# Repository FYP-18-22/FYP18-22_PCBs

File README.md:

This repository holds all our electrical and electronics designs.

Contains files for a main PCB and an actuation PCB.

The main PCB uses an STM32F103CC controller and provides for interfacing with various sensors. It also interacts with our actuation PCB by accepting the zero-crossing detection signal from the actuation PCB and sends back actuation commands to it.

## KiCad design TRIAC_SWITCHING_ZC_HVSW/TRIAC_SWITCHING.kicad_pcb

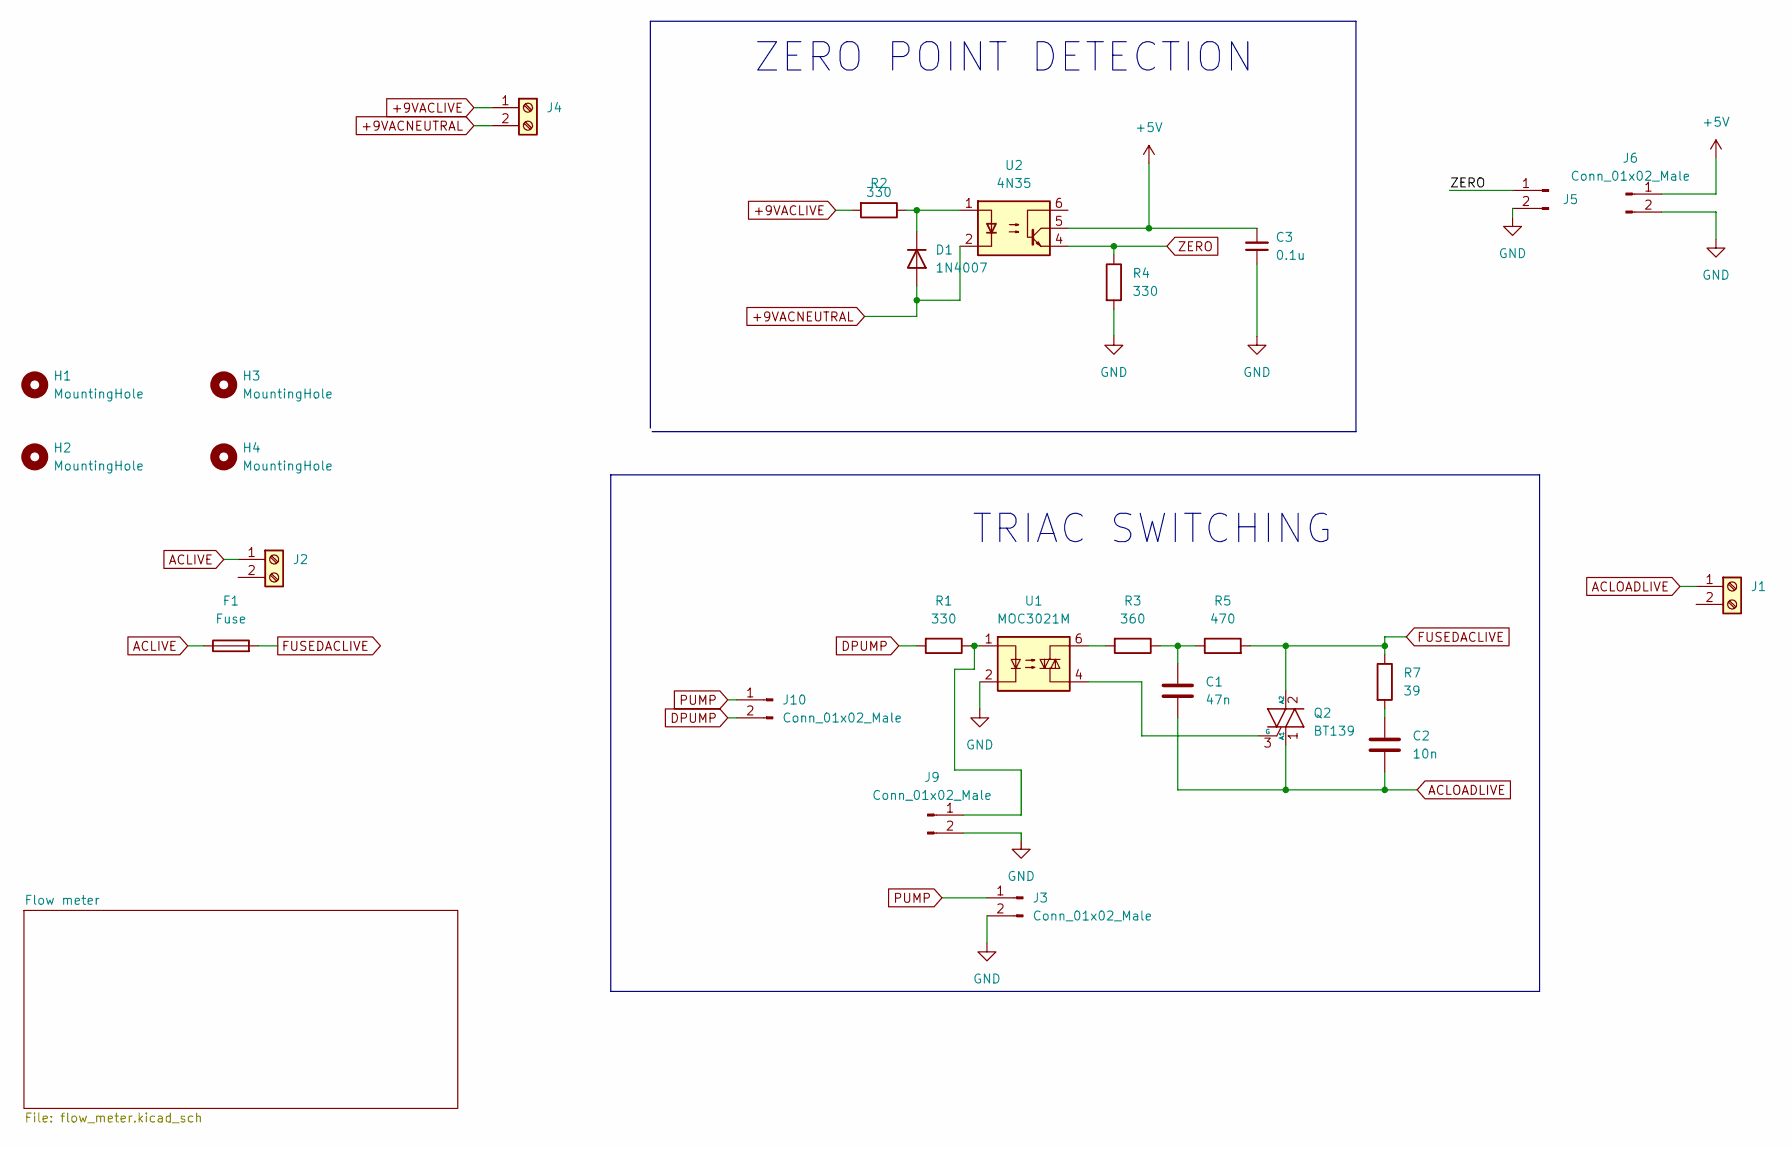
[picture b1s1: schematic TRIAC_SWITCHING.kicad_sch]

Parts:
C1: 47n; CP_Radial_D5.0mm_P2.50mm
C2: 10n; CP_Radial_D5.0mm_P2.50mm
C3: 0.1u; CP_Radial_D5.0mm_P2.50mm
D1: 1N4007; D_DO-41_SOD81_P10.16mm_Horizontal
F1: Fuse; Fuseholder_Cylinder-5x20mm_Stelvio-Kontek_PTF78_Horizontal_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
H1, H2, H3, H4: MountingHole; MountingHole_3.2mm_M3
J1, J2, J4: Screw_Terminal_01x02; TerminalBlock_Phoenix_MKDS-1,5-2-5.08_1x02_P5.08mm_Horizont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
J3, J5, J6, J9, J10: Conn_01x02_Male; PinHeader_1x02_P2.54mm_Vertical
Q2: BT139; TO-220-3_Vertical
R1, R2, R4: 330; R_Axial_DIN0207_L6.3mm_D2.5mm_P10.16mm_Horizontal
R3: 360; R_Axial_DIN0207_L6.3mm_D2.5mm_P10.16mm_Horizontal
R5: 470; R_Axial_DIN0207_L6.3mm_D2.5mm_P10.16mm_Horizontal
R7: 39; R_Axial_DIN0207_L6.3mm_D2.5mm_P10.16mm_Horizontal
U1: MOC3021M; DIP-6_W7.62mm
U2: 4N35; DIP-6_W7.62mm

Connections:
+5V: C3.2, J6.1, U2.5; also elsewhere on the board
+9VACLIVE: J4.1, R2.2
+9VACNEUTRAL: D1.2 (A), J4.2, U2.2
ACLIVE: F1.1, J2.1
ACLOADLIVE: C1.2, C2.2, J1.1, Q2.1 (A1)
DPUMP: J10.2, R1.2
FUSEDACLIVE: F1.2, Q2.2 (A2), R5.2, R7.1
GND: C3.1, J3.2, J5.2, J6.2, J9.2, R4.2, U1.2; also elsewhere on the board
unnamed: C1.1, R3.1, R5.1
unnamed: C2.1, R7.2
unnamed: D1.1 (K), R2.1, U2.1
unnamed: J9.1, R1.1, U1.1
unnamed: Q2.3 (G), U1.4
unnamed: R3.2, U1.6
PUMP: J3.1, J10.1
ZERO: J5.1, R4.1, U2.4

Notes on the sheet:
TRIAC SWITCHING
ZERO POINT DETECTION

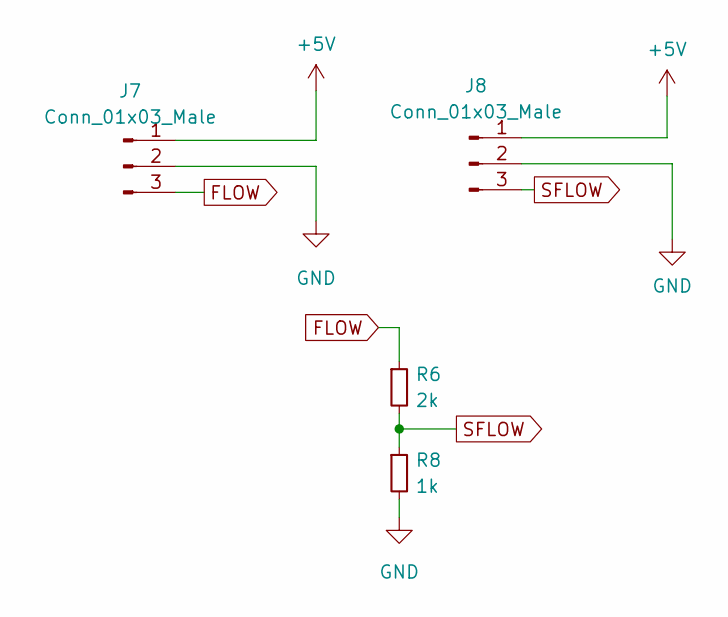
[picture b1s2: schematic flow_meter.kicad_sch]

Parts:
J7, J8: Conn_01x03_Male; PinHeader_1x03_P2.54mm_Vertical
R6: 2k; R_Axial_DIN0207_L6.3mm_D2.5mm_P10.16mm_Horizontal
R8: 1k; R_Axial_DIN0207_L6.3mm_D2.5mm_P10.16mm_Horizontal

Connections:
+5V: J7.1, J8.1; also elsewhere on the board
FLOW: J7.3, R6.1
GND: J7.2, J8.2, R8.2; also elsewhere on the board
SFLOW: J8.3, R6.2, R8.1

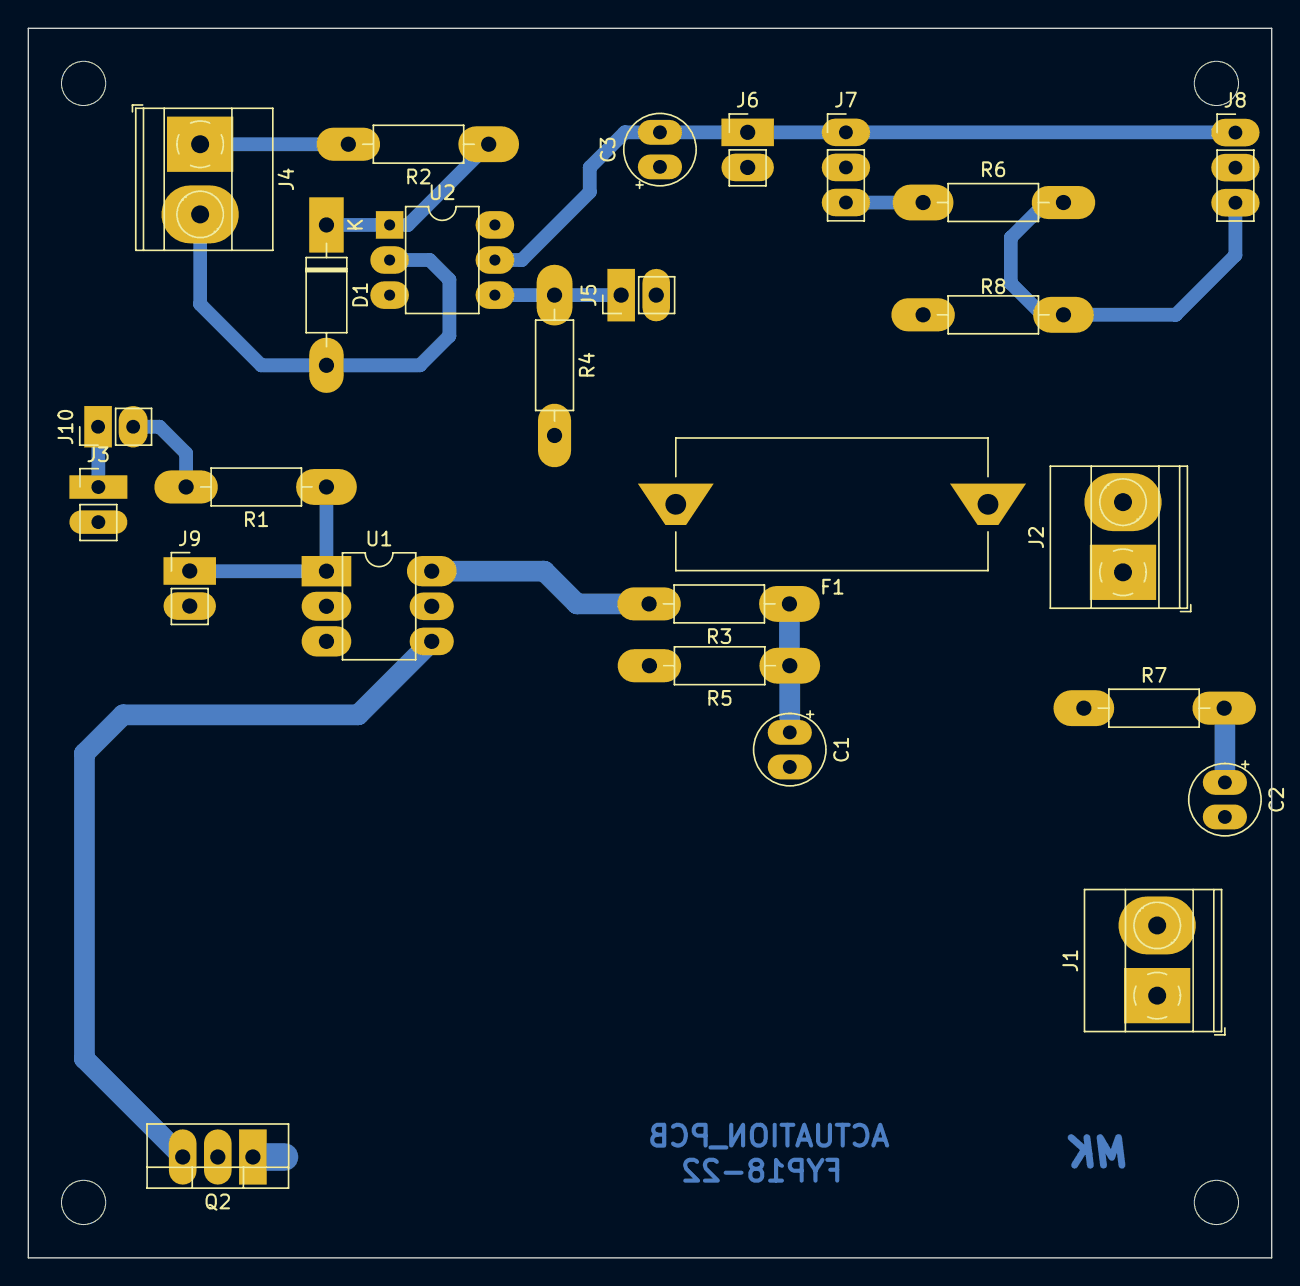
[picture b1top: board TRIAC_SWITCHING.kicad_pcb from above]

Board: 2 copper layers, 90.0 x 89.0 mm, 30 parts (0 on the bottom side), 18 nets.

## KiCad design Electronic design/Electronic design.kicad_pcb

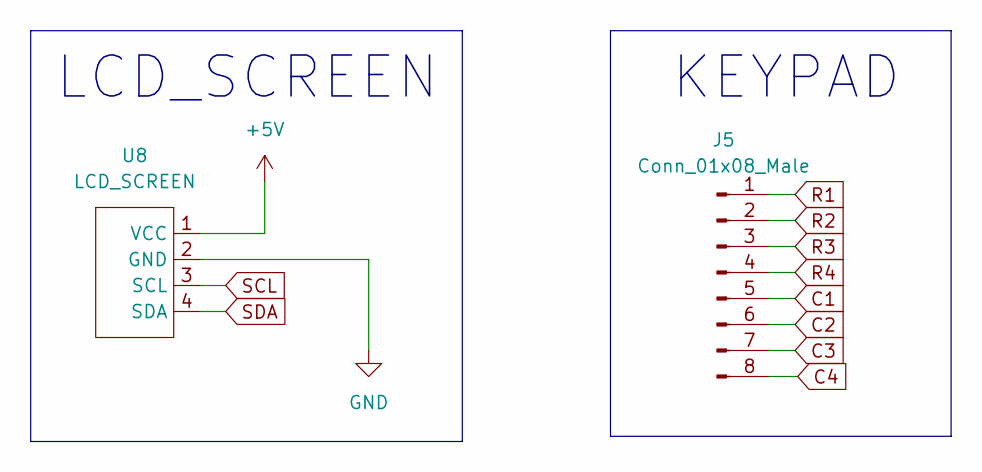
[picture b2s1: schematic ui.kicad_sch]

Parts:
J5: Conn_01x08_Male; PinHeader_1x08_P2.54mm_Vertical
U8: LCD_SCREEN; PinHeader_1x04_P2.54mm_Vertical

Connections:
+5V: U8.1 (VCC); also elsewhere on the board
C1: J5.5; also elsewhere on the board
C2: J5.6; also elsewhere on the board
C3: J5.7; also elsewhere on the board
C4: J5.8; also elsewhere on the board
GND: U8.2 (GND); also elsewhere on the board
R1: J5.1; also elsewhere on the board
R2: J5.2; also elsewhere on the board
R3: J5.3; also elsewhere on the board
R4: J5.4; also elsewhere on the board
SCL: U8.3 (SCL); also elsewhere on the board
SDA: U8.4 (SDA); also elsewhere on the board

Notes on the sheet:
KEYPAD
LCD_SCREEN

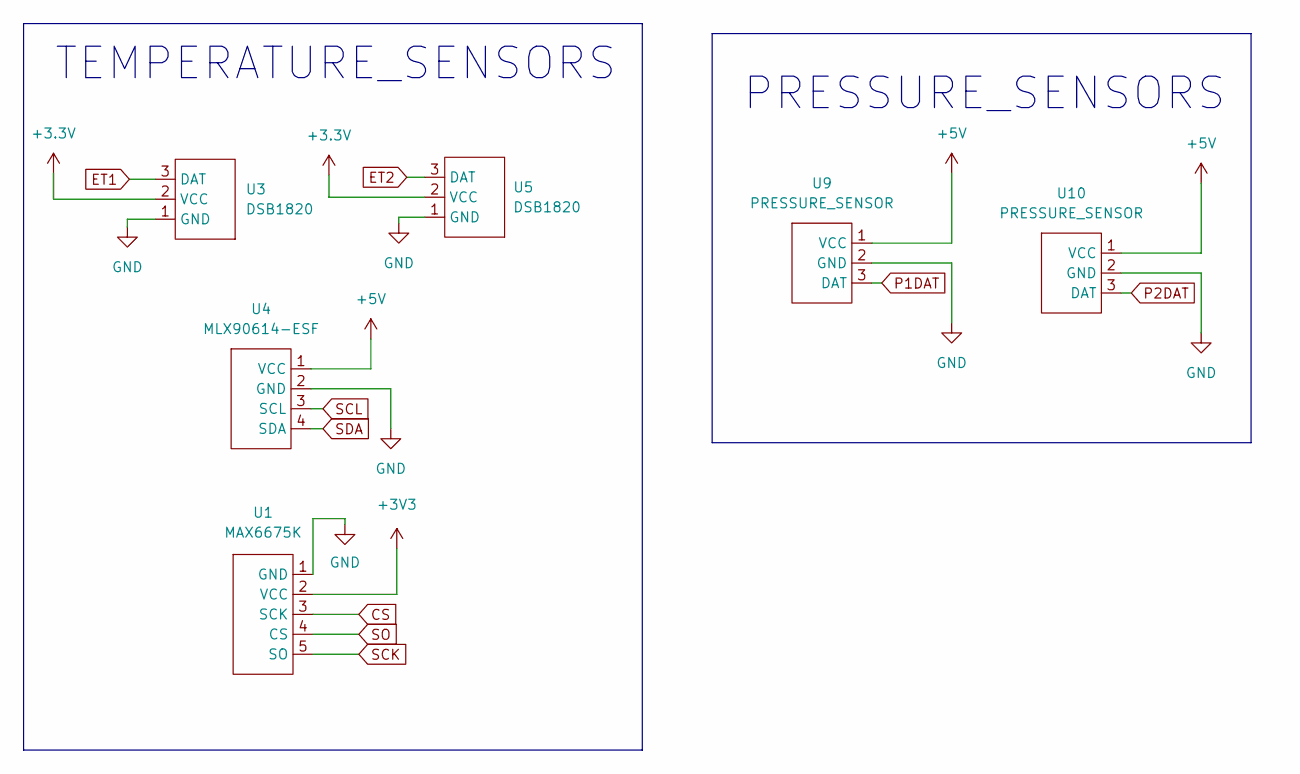
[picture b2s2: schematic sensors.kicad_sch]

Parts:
U1: MAX6675K; PinHeader_1x05_P2.54mm_Vertical
U3, U5: DSB1820; PinHeader_1x03_P2.54mm_Vertical
U4: MLX90614-ESF; PinHeader_1x04_P2.54mm_Vertical
U9, U10: PRESSURE_SENSOR; PinHeader_1x03_P2.54mm_Vertical

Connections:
+5V: U4.1 (VCC), U9.1 (VCC), U10.1 (VCC); also elsewhere on the board
CS: U1.3 (SCK); also elsewhere on the board
ET1: U3.3 (DAT); also elsewhere on the board
ET2: U5.3 (DAT); also elsewhere on the board
GND: U1.1 (GND), U3.1 (GND), U4.2 (GND), U5.1 (GND), U9.2 (GND), U10.2 (GND); also elsewhere on the board
P1DAT: U9.3 (DAT); also elsewhere on the board
P2DAT: U10.3 (DAT); also elsewhere on the board
SCK: U1.5 (SO); also elsewhere on the board
SCL: U4.3 (SCL); also elsewhere on the board
SDA: U4.4 (SDA); also elsewhere on the board
SO: U1.4 (CS); also elsewhere on the board

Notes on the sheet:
PRESSURE_SENSORS
TEMPERATURE_SENSORS

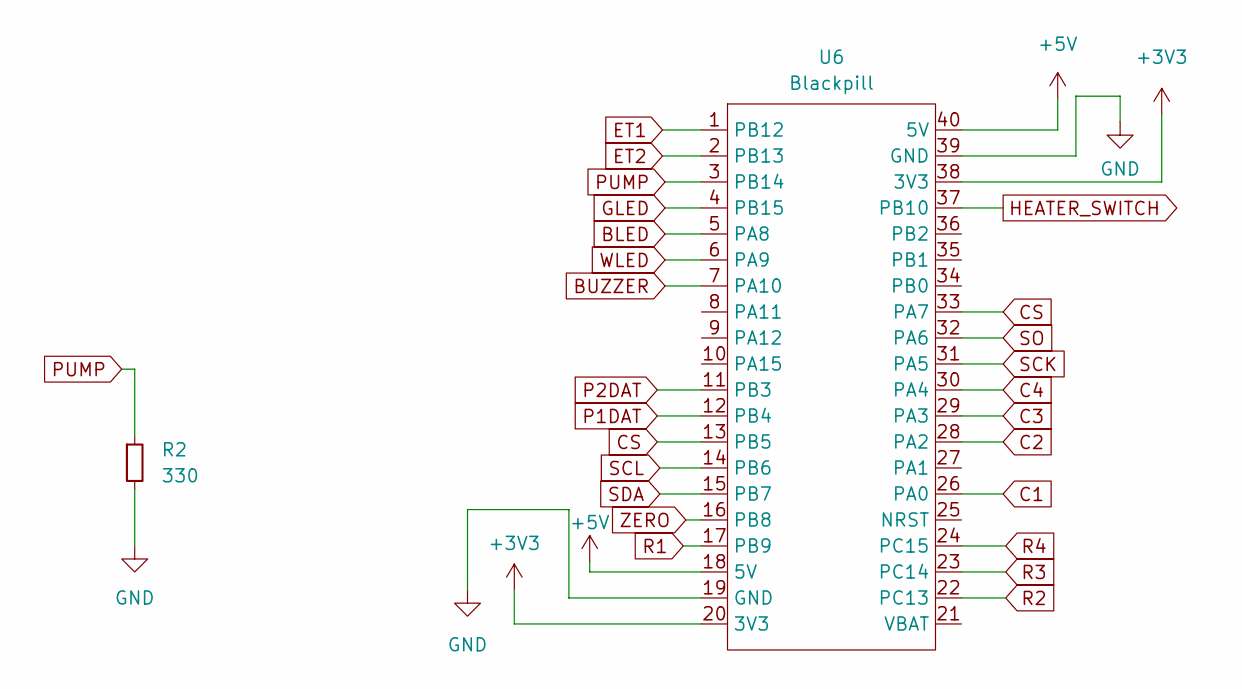
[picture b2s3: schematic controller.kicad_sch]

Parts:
R2: 330; R_Axial_DIN0207_L6.3mm_D2.5mm_P10.16mm_Horizontal
U6: Blackpill

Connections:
+5V: U6.18 (5V), U6.40 (5V); also elsewhere on the board
BLED: U6.5 (PA8); also elsewhere on the board
BUZZER: U6.7 (PA10)
C1: U6.26 (PA0); also elsewhere on the board
C2: U6.28 (PA2); also elsewhere on the board
C3: U6.29 (PA3); also elsewhere on the board
C4: U6.30 (PA4); also elsewhere on the board
CS: U6.13 (PB5), U6.33 (PA7); also elsewhere on the board
ET1: U6.1 (PB12); also elsewhere on the board
ET2: U6.2 (PB13); also elsewhere on the board
GLED: U6.4 (PB15); also elsewhere on the board
GND: R2.2, U6.19 (GND), U6.39 (GND); also elsewhere on the board
HEATER_SWITCH: U6.37 (PB10); also elsewhere on the board
P1DAT: U6.12 (PB4); also elsewhere on the board
P2DAT: U6.11 (PB3); also elsewhere on the board
PUMP: R2.1, U6.3 (PB14); also elsewhere on the board
R1: U6.17 (PB9); also elsewhere on the board
R2: U6.22 (PC13); also elsewhere on the board
R3: U6.23 (PC14); also elsewhere on the board
R4: U6.24 (PC15); also elsewhere on the board
SCK: U6.31 (PA5); also elsewhere on the board
SCL: U6.14 (PB6); also elsewhere on the board
SDA: U6.15 (PB7); also elsewhere on the board
SO: U6.32 (PA6); also elsewhere on the board
WLED: U6.6 (PA9); also elsewhere on the board
ZERO: U6.16 (PB8); also elsewhere on the board

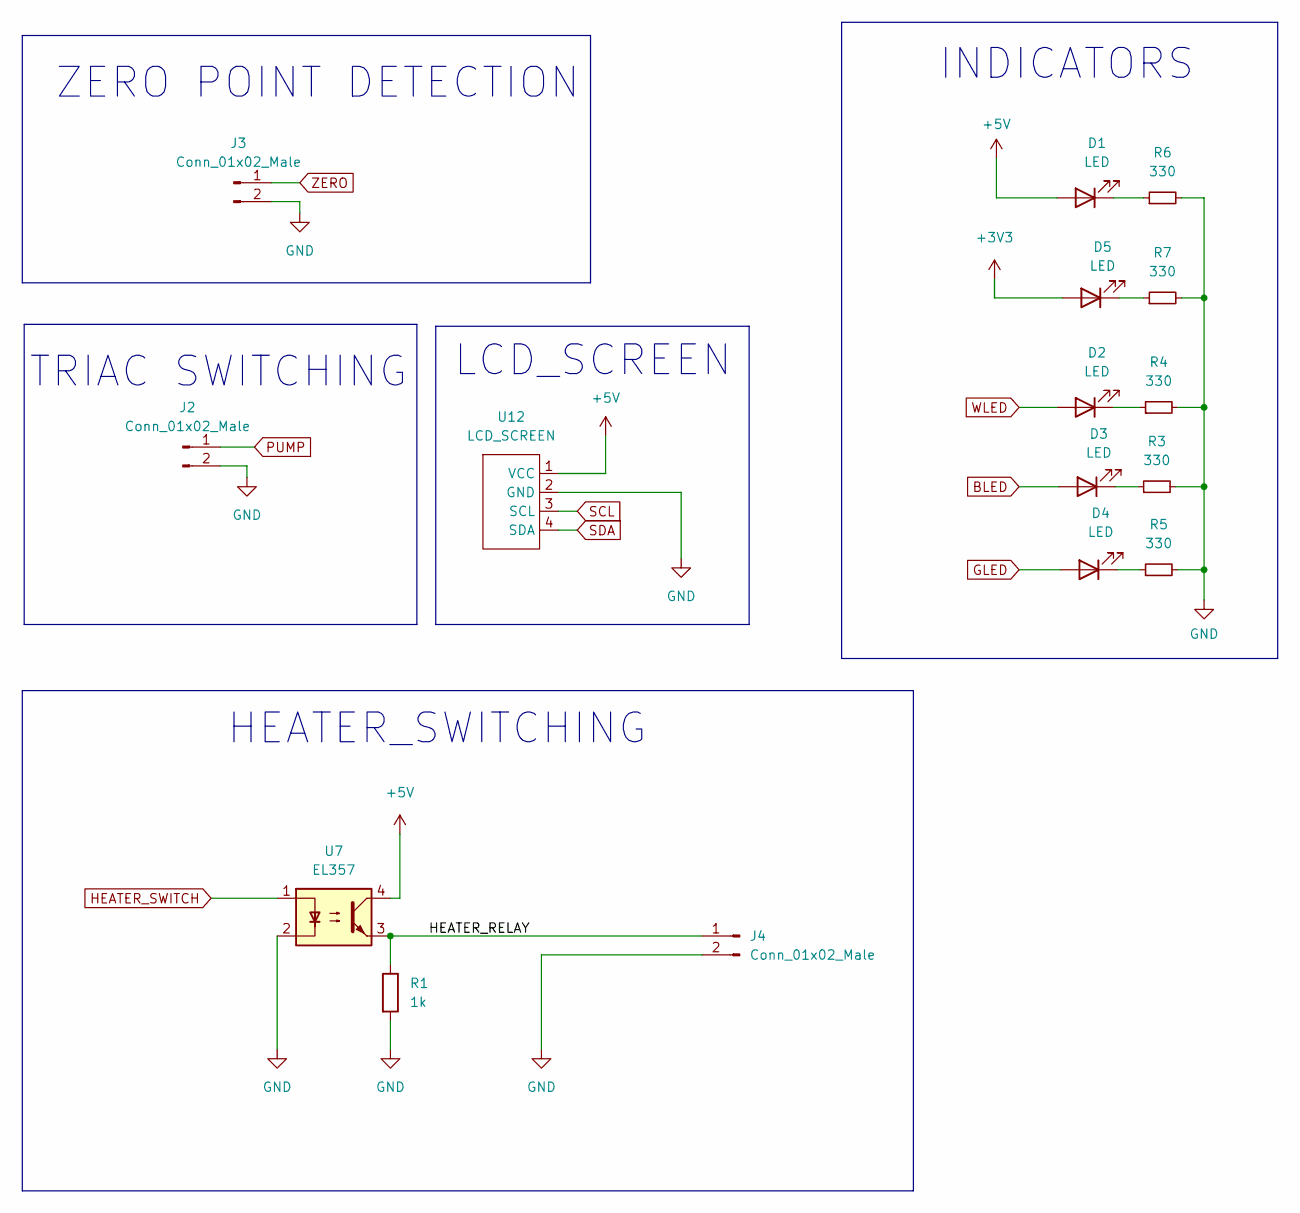
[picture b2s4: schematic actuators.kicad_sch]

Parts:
D1, D2, D3, D4, D5: LED; PinHeader_1x02_P2.54mm_Vertical
J2, J3, J4: Conn_01x02_Male; PinHeader_1x02_P2.54mm_Vertical
R1: 1k; R_Axial_DIN0207_L6.3mm_D2.5mm_P10.16mm_Horizontal
R3, R4, R5, R6, R7: 330; R_Axial_DIN0207_L6.3mm_D2.5mm_P10.16mm_Horizontal
U7: EL357; DIP-4_W7.62mm; LCSC Part Number C6649
U12: LCD_SCREEN; PinHeader_1x04_P2.54mm_Vertical

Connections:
+5V: D1.2 (A), U7.4, U12.1 (VCC); also elsewhere on the board
/Actuators/HEATER_RELAY: J4.1, R1.1, U7.3
BLED: D3.2 (A); also elsewhere on the board
GLED: D4.2 (A); also elsewhere on the board
GND: J2.2, J3.2, J4.2, R1.2, R3.2, R4.2, R5.2, R6.2, R7.2, U7.2, U12.2 (GND); also elsewhere on the board
HEATER_SWITCH: U7.1; also elsewhere on the board
unnamed: D1.1 (K), R6.1
unnamed: D2.1 (K), R4.1
unnamed: D3.1 (K), R3.1
unnamed: D4.1 (K), R5.1
unnamed: D5.1 (K), R7.1
PUMP: J2.1; also elsewhere on the board
SCL: U12.3 (SCL); also elsewhere on the board
SDA: U12.4 (SDA); also elsewhere on the board
WLED: D2.2 (A); also elsewhere on the board
ZERO: J3.1; also elsewhere on the board

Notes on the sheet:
HEATER_SWITCHING
ZERO POINT DETECTION
INDICATORS
LCD_SCREEN
TRIAC SWITCHING

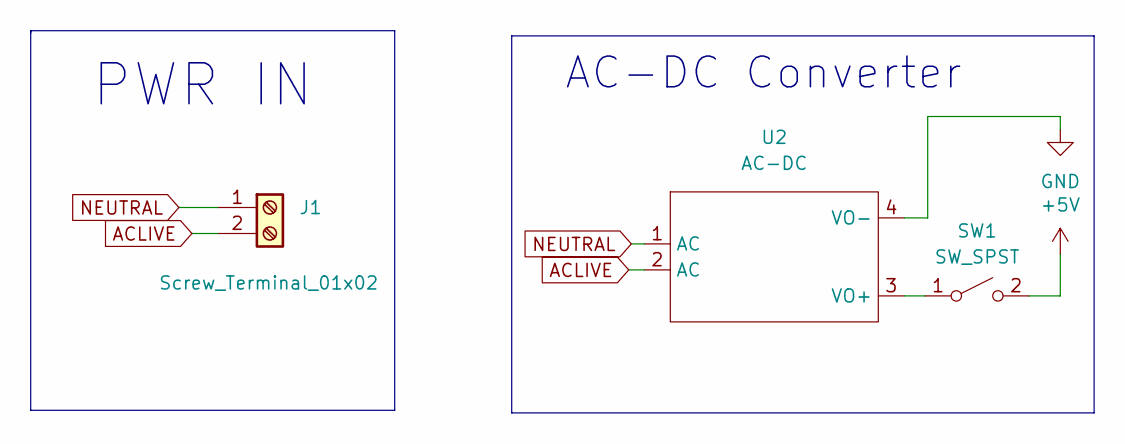
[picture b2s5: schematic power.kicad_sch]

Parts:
J1: Screw_Terminal_01x02; TerminalBlock_Phoenix_MKDS-1,5-2-5.08_1x02_P5.08mm_Horizont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
SW1: SW_SPST; KCD1 switch
U2: AC-DC; AC_DC

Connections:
+5V: SW1.2 (B); also elsewhere on the board
ACLIVE: J1.2, U2.2 (AC)
GND: U2.4 (VO-); also elsewhere on the board
NEUTRAL: J1.1, U2.1 (AC)
unnamed: SW1.1 (A), U2.3 (VO+)

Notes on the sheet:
PWR IN
AC-DC Converter

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
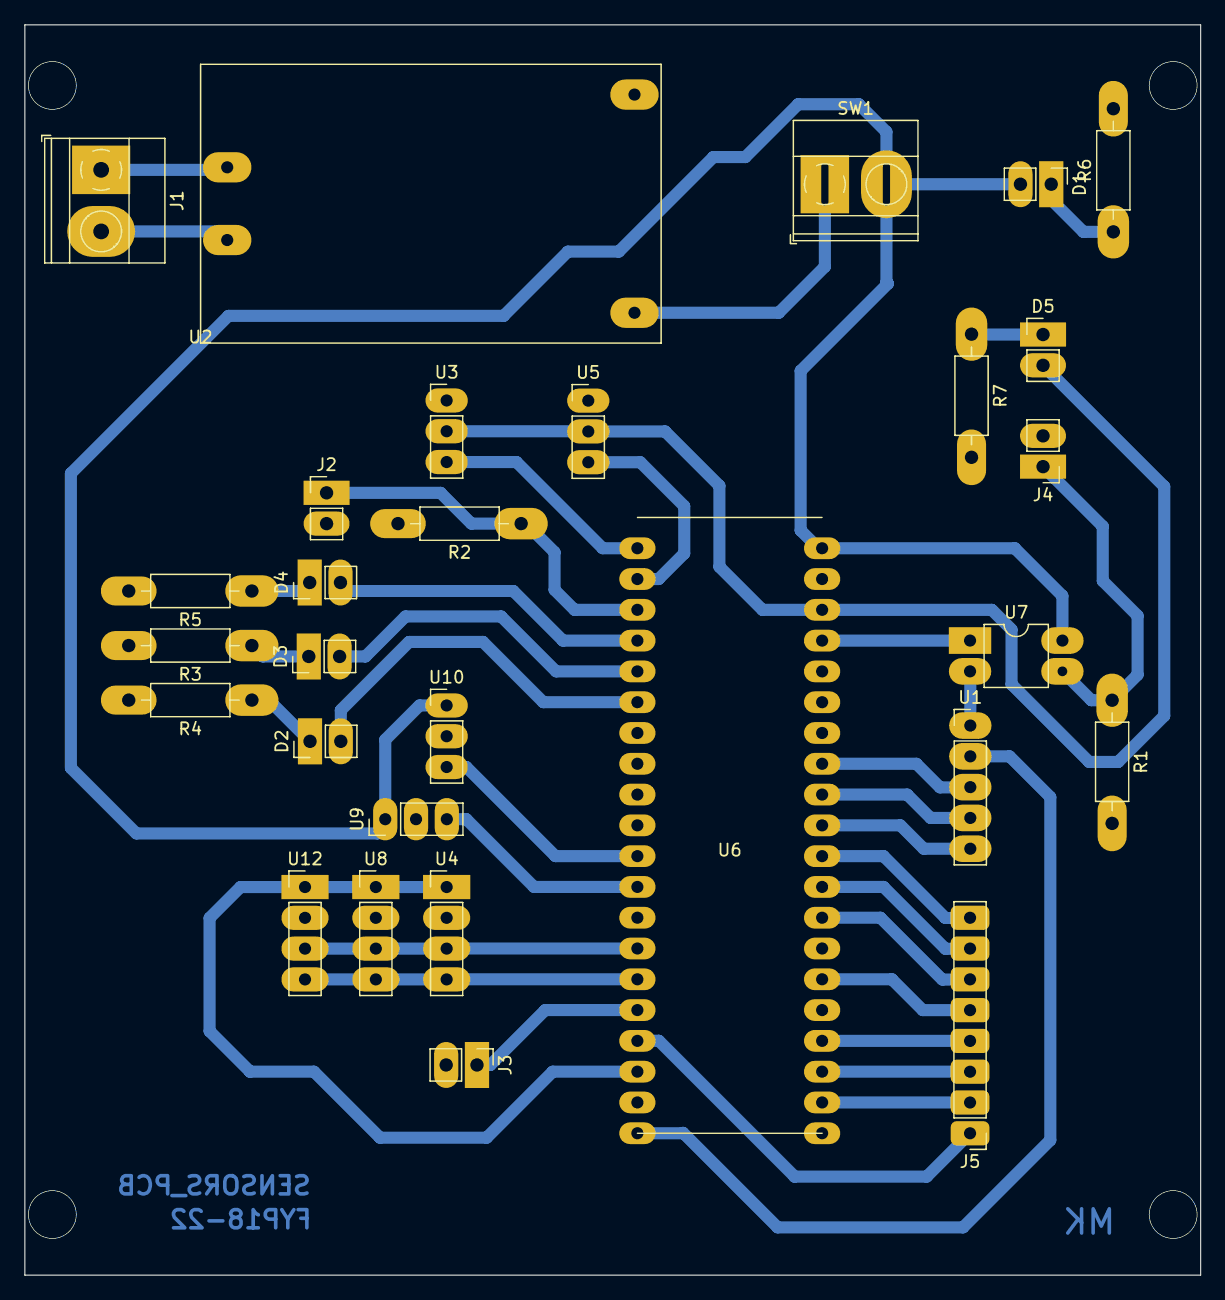
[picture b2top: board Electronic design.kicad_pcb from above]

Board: 2 copper layers, 97.0 x 103.1 mm, 29 parts (0 on the bottom side), 35 nets.

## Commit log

2022-12-10 Adding gitignore
2022-12-10 Adding README file
2022-12-10 Electronics for the presentstion
2023-01-04 Last changes
2023-01-22 Removing old png
